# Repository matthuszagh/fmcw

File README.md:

See doc/fmcw-radar.pdf

#### TODO

* Investigate the possibility of performing FFT processing on the FPGA. This may require an FPGA
  with a higher LUT count. Investigate if the e.g. 50T is pin compatible with the current 15T. The
  goal would be to have the host computer plot the radar output in real-time rather than relying on
  post-processing. It might also be worth looking at the ECP5 FPGA, which seems to give you more per
  dollar and has better open source support.
* Formally verify FPGA code with [SymbiYosys](https://symbiyosys.readthedocs.io/en/latest/quickstart.html).
* Write PC code.
* Consider using a soft processor
  (e.g. [picorv32](https://github.com/cliffordwolf/picorv32/tree/master/picosoc)) for the FPGA
  control logic and configuration.
* Create RF simulations with OpenEMS.
* Create script to ensure all FPGA pins are connected correctly using a JTAG boundary scan.
* Modify FPGA code to allow configuration of the radar via a connected PC, rather than baking the
  logic directly into the FPGA code. This has the benefit that the FPGA logic does not need to be
  resynthesized each time the configurations are changed.
* Improve documentation.
* Remove old files only needed in the previous iteration of this project.
* 3D print mount for radar. This should include a case for the PCB and a mount for the antenna.

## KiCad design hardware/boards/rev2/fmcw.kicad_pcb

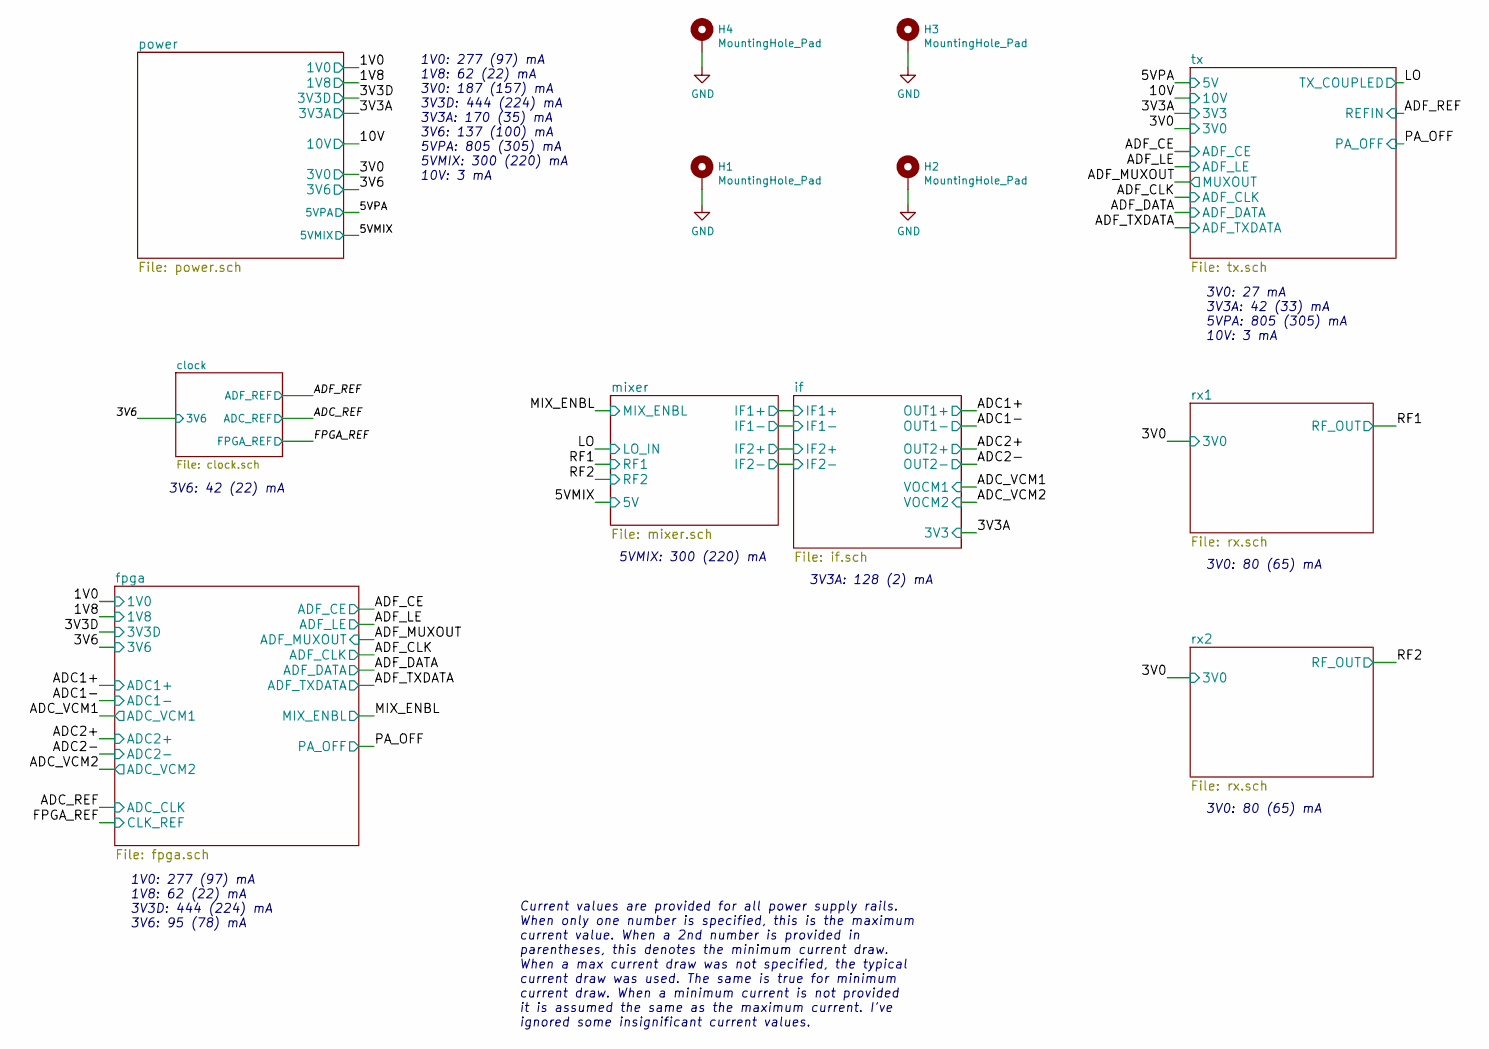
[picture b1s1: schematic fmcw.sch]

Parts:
H1, H2, H3, H4: MountingHole_Pad; MountingHole_3.2mm_M3_Pad_Via

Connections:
GND: H1.1, H2.1, H3.1, H4.1; also elsewhere on the board

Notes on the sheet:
1V0: 277 (97) mA 1V8: 62 (22) mA 3V3D: 444 (224) mA 3V6: 95 (78) mA
3V6: 42 (22) mA
1V0: 277 (97) mA 1V8: 62 (22) mA 3V0: 187 (157) mA 3V3D: 444 (224) mA 3V3A: 170 (35) mA 3V6: 137 (100) mA 5VPA: 805 (305) mA 5VMIX: 300 (220) mA 10V: 3 mA
Current values are provided for all power supply rails. When only one number is specified, this is the maximum current value. When a 2nd number is provided in parentheses, this denotes the minimum current draw. When a max current draw was not specified, the typical current draw was used. The same i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
5VMIX: 300 (220) mA
3V3A: 128 (2) mA
3V0: 27 mA 3V3A: 42 (33) mA 5VPA: 805 (305) mA 10V: 3 mA
3V0: 80 (65) mA

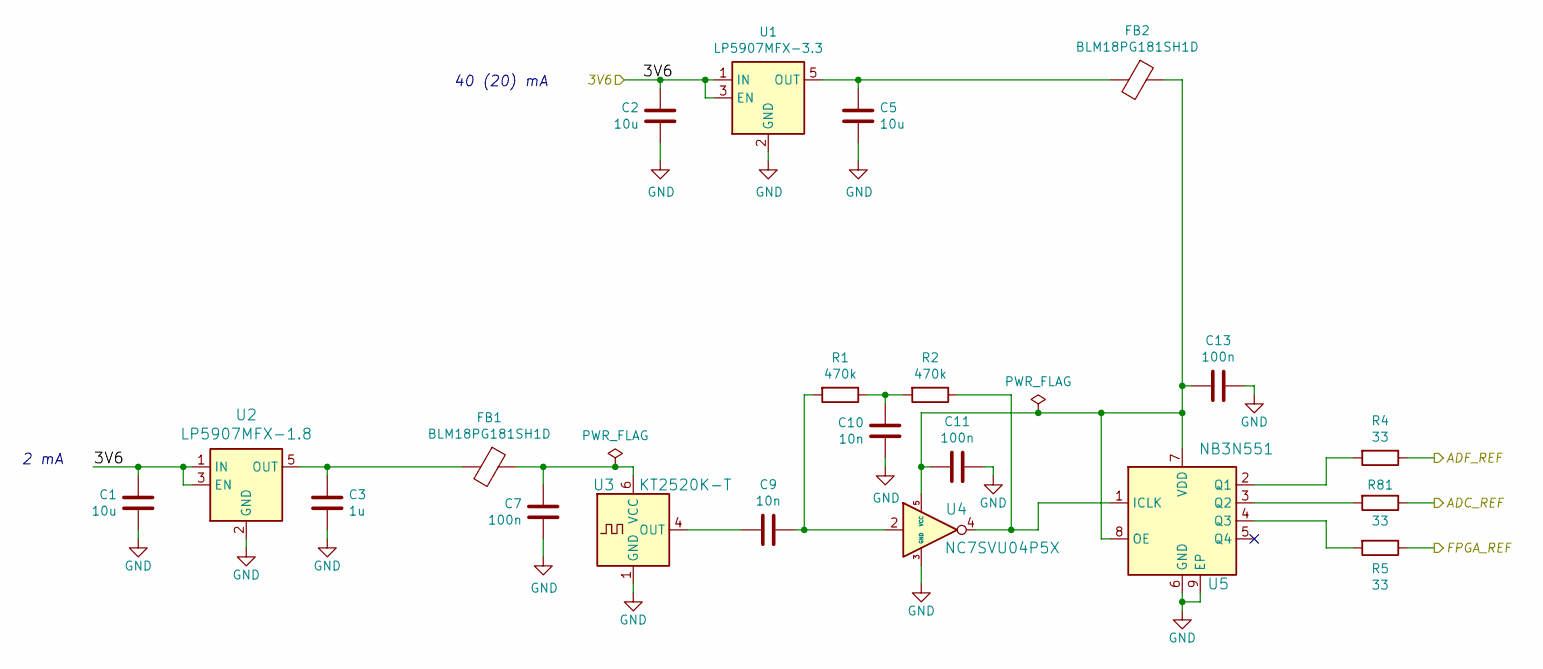
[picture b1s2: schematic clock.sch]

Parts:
C1, C2, C5: 10u; C_0805_2012Metric
C3: 1u; C_0805_2012Metric
C7, C11, C13: 100n; C_0402_1005Metric
C9, C10: 10n; C_0402_1005Metric
FB1, FB2: BLM18PG181SH1D; L_0603_1608Metric
R1, R2: 470k; R_0402_1005Metric
R4, R5, R81: 33; R_0402_1005Metric
U1: LP5907MFX-3.3; SOT-23-5
U2: LP5907MFX-1.8; SOT-23-5
U3: KT2520K-T; Oscillator_SMD_Kyocera_2520-6Pin_2.5x2.0mm
U4: NC7SVU04P5X; SOT-353_SC-70-5
U5: NB3N551; DFN-8-1EP_2x2mm_P0.5mm_EP0.9x1.3mm

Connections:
/3V6: C1.1, C2.1, U1.1 (IN), U1.3 (EN), U2.1 (IN), U2.3 (EN); also elsewhere on the board
/ADC_REF: R81.1; also elsewhere on the board
/ADF_REF: R4.1; also elsewhere on the board
/FPGA_REF: R5.1; also elsewhere on the board
GND: C1.2, C2.2, C3.2, C5.2, C7.1, C10.1, C11.1, C13.1, U1.2 (GND), U2.2 (GND), U3.1 (GND), U3.3 (GND), U4.3 (GND), U5.6 (GND), U5.9 (EP); also elsewhere on the board
unnamed: C3.1, FB1.2, U2.5 (OUT)
unnamed: C5.1, FB2.2, U1.5 (OUT)
unnamed: C7.2, FB1.1, U3.6 (VCC)
unnamed: C9.1, R1.2, U4.2
unnamed: C9.2, U3.4 (OUT)
unnamed: C10.2, R1.1, R2.2
unnamed: C11.2, C13.2, FB2.1, U4.5 (VCC), U5.7 (VDD), U5.8 (OE)
unnamed: R2.1, U4.4, U5.1 (ICLK)
unnamed: R4.2, U5.2 (Q1)
unnamed: R5.2, U5.4 (Q3)
unnamed: R81.2, U5.3 (Q2)

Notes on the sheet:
2 mA
40 (20) mA

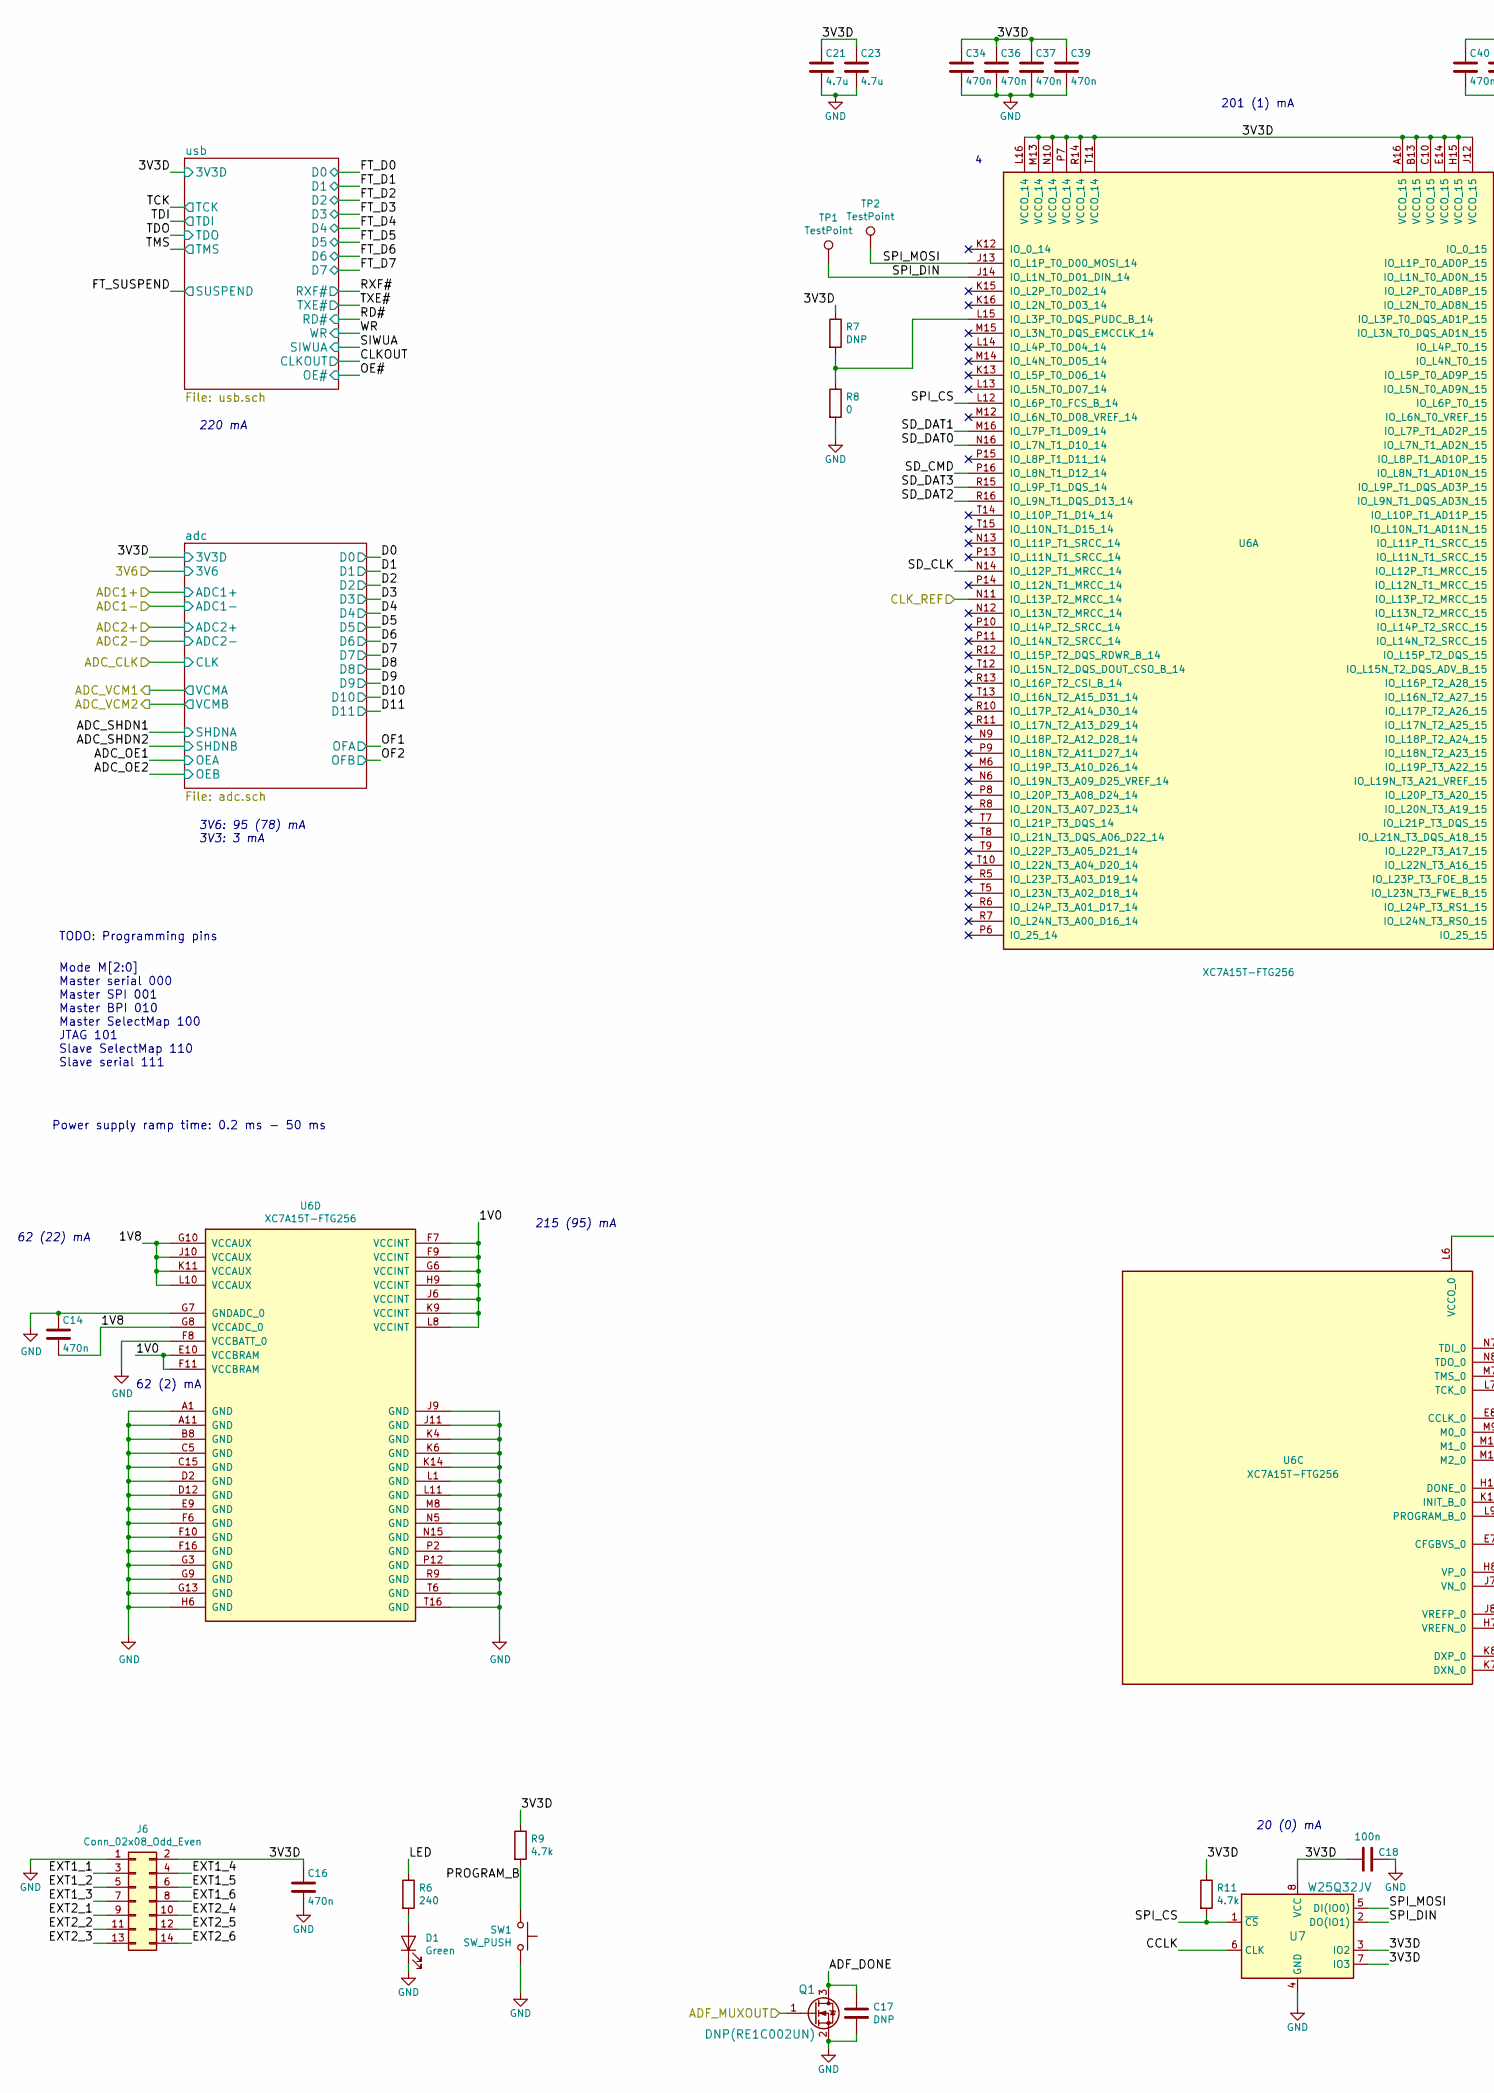
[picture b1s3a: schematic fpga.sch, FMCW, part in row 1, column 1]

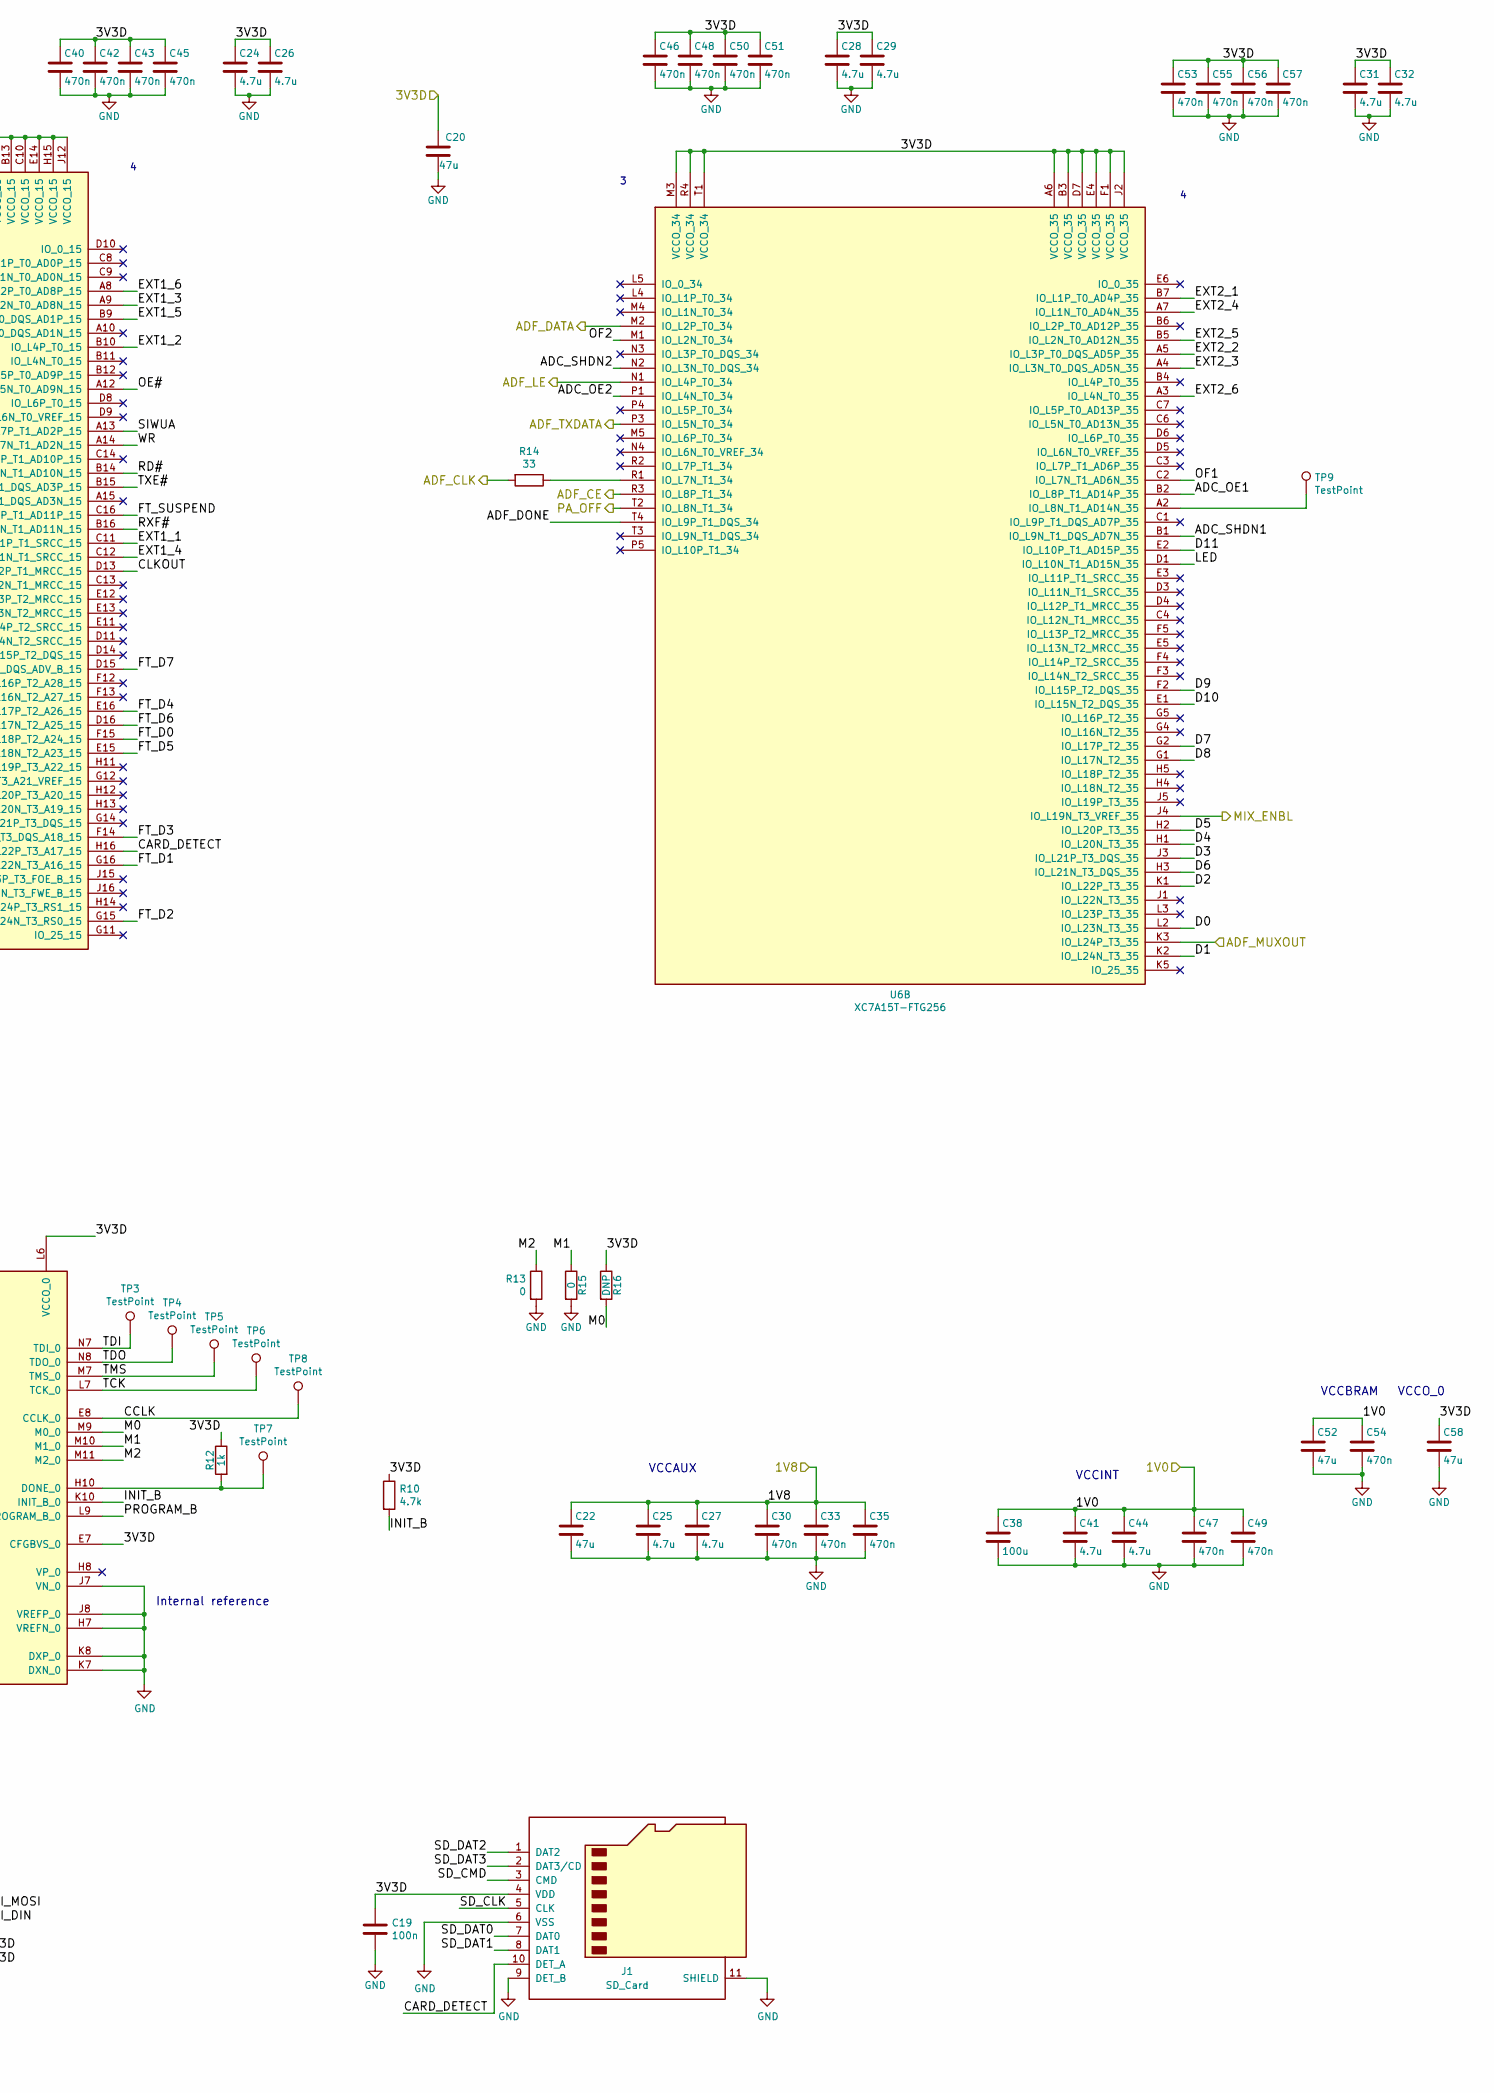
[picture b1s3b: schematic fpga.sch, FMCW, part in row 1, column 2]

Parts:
C14, C16, C30, C33, C34, C35, C36, C37, C39, C40, C42, C43, C45, C46, C47, C48, C49, C50, C51, C53, C54, C55, C56, C57: 470n; C_0603_1608Metric
C17: DNP; C_0402_1005Metric
C18, C19: 100n; C_0402_1005Metric
C20, C22, C52, C58: 47u; C_1206_3216Metric
C21, C23, C24, C25, C26, C27, C28, C29, C31, C32, C41, C44: 4.7u; C_0805_2012Metric
C38: 100u; C_1210_3225Metric
D1: Green; LED_0603_1608Metric
J1: SD_Card; microSD_HC_Hirose_DM3BT-DSF-PEJS
J6: Conn_02x08_Odd_Even; PinHeader_2x07_P2.54mm_Vertical
Q1: DNP(RE1C002UN); SOT-416
R6: 240; R_0402_1005Metric
R7, R16: DNP; R_0402_1005Metric
R8, R13, R15: 0; R_0402_1005Metric
R9, R10, R11: 4.7k; R_0402_1005Metric
R12: 1k; R_0402_1005Metric
R14: 33; R_0402_1005Metric
SW1: SW_PUSH; SW_SPST_PTS810
TP1, TP2, TP3, TP4, TP5, TP6, TP7, TP8, TP9: TestPoint; TestPoint_Loop_D1.80mm_Drill1.0mm_Beaded
U6: XC7A15T-FTG256; Xilinx_FTG256
U7: W25Q32JV; SOIJ-8_5.3x5.3mm_P1.27mm

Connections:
/1V0: C38.1, C41.1, C44.1, C47.1, C49.1, C52.1, C54.1, U6.E10 (VCCBRAM), U6.F7 (VCCINT), U6.F9 (VCCINT), U6.F11 (VCCBRAM), U6.G6 (VCCINT), U6.H9 (VCCINT), U6.J6 (VCCINT), U6.K9 (VCCINT), U6.L8 (VCCINT); also elsewhere on the board
/1V8: C14.2, C22.1, C25.1, C27.1, C30.1, C33.1, C35.1, U6.G8 (VCCADC_0), U6.G10 (VCCAUX), U6.J10 (VCCAUX), U6.K11 (VCCAUX), U6.L10 (VCCAUX); also elsewhere on the board
/ADF_CE: U6.R3 (IO_L8P_T1_34); also elsewhere on the board
/ADF_CLK: R14.2; also elsewhere on the board
/ADF_DATA: U6.M2 (IO_L2P_T0_34); also elsewhere on the board
/ADF_LE: U6.N1 (IO_L4P_T0_34); also elsewhere on the board
/ADF_MUXOUT: Q1.1 (G), U6.K3 (IO_L24P_T3_35); also elsewhere on the board
/ADF_TXDATA: U6.P3 (IO_L5N_T0_34); also elsewhere on the board
/FPGA_REF: U6.N11 (IO_L13P_T2_MRCC_14); also elsewhere on the board
/MIX_ENBL: U6.J4 (IO_L19N_T3_VREF_35); also elsewhere on the board
/PA_OFF: U6.T2 (IO_L8N_T1_34); also elsewhere on the board
/fpga/ADC_OE1: U6.B2 (IO_L8P_T1_AD14P_35); also elsewhere on the board
/fpga/ADC_OE2: U6.P1 (IO_L4N_T0_34); also elsewhere on the board
/fpga/ADC_SHDN1: U6.B1 (IO_L9N_T1_DQS_AD7N_35); also elsewhere on the board
/fpga/ADC_SHDN2: U6.N2 (IO_L3N_T0_DQS_34); also elsewhere on the board
/fpga/ADF_DONE: C17.1, Q1.3 (D), U6.T4 (IO_L9P_T1_DQS_34)
/fpga/CARD_DETECT: J1.10 (DET_A), U6.H16 (IO_L22P_T3_A17_15)
/fpga/CCLK: TP8.1, U6.E8 (CCLK_0), U7.6 (CLK)
/fpga/CLKOUT: U6.D13 (IO_L12P_T1_MRCC_15); also elsewhere on the board
/fpga/D0: U6.L2 (IO_L23N_T3_35); also elsewhere on the board
/fpga/D1: U6.K2 (IO_L24N_T3_35); also elsewhere on the board
/fpga/D2: U6.K1 (IO_L22P_T3_35); also elsewhere on the board
/fpga/D3: U6.J3 (IO_L21P_T3_DQS_35); also elsewhere on the board
/fpga/D4: U6.H1 (IO_L20N_T3_35); also elsewhere on the board
/fpga/D5: U6.H2 (IO_L20P_T3_35); also elsewhere on the board
/fpga/D6: U6.H3 (IO_L21N_T3_DQS_35); also elsewhere on the board
/fpga/D7: U6.G2 (IO_L17P_T2_35); also elsewhere on the board
/fpga/D8: U6.G1 (IO_L17N_T2_35); also elsewhere on the board
/fpga/D9: U6.F2 (IO_L15P_T2_DQS_35); also elsewhere on the board
/fpga/D10: U6.E1 (IO_L15N_T2_DQS_35); also elsewhere on the board
/fpga/D11: U6.E2 (IO_L10P_T1_AD15P_35); also elsewhere on the board
/fpga/EXT1_1: J6.3, U6.C11 (IO_L11P_T1_SRCC_15)
/fpga/EXT1_2: J6.5, U6.B10 (IO_L4P_T0_15)
/fpga/EXT1_3: J6.7, U6.A9 (IO_L2N_T0_AD8N_15)
/fpga/EXT1_4: J6.4, U6.C12 (IO_L11N_T1_SRCC_15)
/fpga/EXT1_5: J6.6, U6.B9 (IO_L3P_T0_DQS_AD1P_15)
/fpga/EXT1_6: J6.8, U6.A8 (IO_L2P_T0_AD8P_15)
/fpga/EXT2_1: J6.9, U6.B7 (IO_L1P_T0_AD4P_35)
/fpga/EXT2_2: J6.11, U6.A5 (IO_L3P_T0_DQS_AD5P_35)
/fpga/EXT2_3: J6.13, U6.A4 (IO_L3N_T0_DQS_AD5N_35)
/fpga/EXT2_4: J6.10, U6.A7 (IO_L1N_T0_AD4N_35)
/fpga/EXT2_5: J6.12, U6.B5 (IO_L2N_T0_AD12N_35)
/fpga/EXT2_6: J6.14, U6.A3 (IO_L4N_T0_35)
/fpga/FT_D0: U6.F15 (IO_L18P_T2_A24_15); also elsewhere on the board
/fpga/FT_D1: U6.G16 (IO_L22N_T3_A16_15); also elsewhere on the board
/fpga/FT_D2: U6.G15 (IO_L24N_T3_RS0_15); also elsewhere on the board
/fpga/FT_D3: U6.F14 (IO_L21N_T3_DQS_A18_15); also elsewhere on the board
/fpga/FT_D4: U6.E16 (IO_L17P_T2_A26_15); also elsewhere on the board
/fpga/FT_D5: U6.E15 (IO_L18N_T2_A23_15); also elsewhere on the board
/fpga/FT_D6: U6.D16 (IO_L17N_T2_A25_15); also elsewhere on the board
/fpga/FT_D7: U6.D15 (IO_L15N_T2_DQS_ADV_B_15); also elsewhere on the board
/fpga/FT_SUSPEND: U6.C16 (IO_L10P_T1_AD11P_15); also elsewhere on the board
/fpga/INIT_B: R10.2, U6.K10 (INIT_B_0)
/fpga/LED: R6.1, U6.D1 (IO_L10N_T1_AD15N_35)
/fpga/M0: R16.2, U6.M9 (M0_0)
/fpga/M1: R15.1, U6.M10 (M1_0)
/fpga/M2: R13.1, U6.M11 (M2_0)
/fpga/OE#: U6.A12 (IO_L5N_T0_AD9N_15); also elsewhere on the board
/fpga/OF1: U6.C2 (IO_L7N_T1_AD6N_35); also elsewhere on the board
/fpga/OF2: U6.M1 (IO_L2N_T0_34); also elsewhere on the board
/fpga/PROGRAM_B: R9.2, SW1.1, U6.L9 (PROGRAM_B_0)
/fpga/RD#: U6.B14 (IO_L8N_T1_AD10N_15); also elsewhere on the board
/fpga/RXF#: U6.B16 (IO_L10N_T1_AD11N_15); also elsewhere on the board
/fpga/SD_CLK: J1.5 (CLK), U6.N14 (IO_L12P_T1_MRCC_14)
/fpga/SD_CMD: J1.3 (CMD), U6.P16 (IO_L8N_T1_D12_14)
/fpga/SD_DAT0: J1.7 (DAT0), U6.N16 (IO_L7N_T1_D10_14)
/fpga/SD_DAT1: J1.8 (DAT1), U6.M16 (IO_L7P_T1_D09_14)
/fpga/SD_DAT2: J1.1 (DAT2), U6.R16 (IO_L9N_T1_DQS_D13_14)
/fpga/SD_DAT3: J1.2 (DAT3/CD), U6.R15 (IO_L9P_T1_DQS_14)
/fpga/SIWUA: U6.A13 (IO_L7P_T1_AD2P_15); also elsewhere on the board
/fpga/SPI_CS: R11.2, U6.L12 (IO_L6P_T0_FCS_B_14), U7.1 (~CS)
/fpga/SPI_DIN: TP1.1, U6.J14 (IO_L1N_T0_D01_DIN_14), U7.2 (DO(IO1))
/fpga/SPI_MOSI: TP2.1, U6.J13 (IO_L1P_T0_D00_MOSI_14), U7.5 (DI(IO0))
/fpga/TCK: TP6.1, U6.L7 (TCK_0); also elsewhere on the board
/fpga/TDI: TP3.1, U6.N7 (TDI_0); also elsewhere on the board
/fpga/TDO: TP4.1, U6.N8 (TDO_0); also elsewhere on the board
/fpga/TMS: TP5.1, U6.M7 (TMS_0); also elsewhere on the board
/fpga/TXE#: U6.B15 (IO_L9P_T1_DQS_AD3P_15); also elsewhere on the board
/fpga/WR: U6.A14 (IO_L7N_T1_AD2N_15); also elsewhere on the board
GND: C14.1, C16.2, C17.2, C18.1, C19.2, C20.2, C21.2, C22.2, C23.2, C24.2, C25.2, C26.2, C27.2, C28.2, C29.2, C30.2, C31.2, C32.2, C33.2, C34.2, C35.2, C36.2, C37.2, C38.2, C39.2, C40.2, C41.2, C42.2, C43.2, C44.2, C45.2, C46.2, C47.2, C48.2, C49.2, C50.2, C51.2, C52.2, C53.2, C54.2, C55.2, C56.2, C57.2, C58.2, D1.1 (K), J1.6 (VSS), J1.9 (DET_B), J1.11 (SHIELD), J6.1, Q1.2 (S), R8.2, R13.2, R15.2, SW1.2, U6.A1 (GND), U6.A11 (GND), U6.B8 (GND), U6.C5 (GND), U6.C15 (GND), U6.D2 (GND), U6.D12 (GND), U6.E9 (GND), U6.F6 (GND), U6.F8 (VCCBATT_0), U6.F10 (GND), U6.F16 (GND), U6.G3 (GND), U6.G7 (GNDADC_0), U6.G9 (GND), U6.G13 (GND), U6.H6 (GND), U6.H7 (VREFN_0), U6.J7 (VN_0), U6.J8 (VREFP_0), U6.J9 (GND), U6.J11 (GND), U6.K4 (GND), U6.K6 (GND), U6.K7 (DXN_0), U6.K8 (DXP_0), U6.K14 (GND), U6.L1 (GND), U6.L11 (GND), U6.M8 (GND), U6.N5 (GND), U6.N15 (GND), U6.P2 (GND), U6.P12 (GND), U6.R9 (GND), U6.T6 (GND), U6.T16 (GND), U7.4 (GND); also elsewhere on the board
unnamed: D1.2 (A), R6.2
unnamed: R7.2, R8.1, U6.L15 (IO_L3P_T0_DQS_PUDC_B_14)
unnamed: R12.2, TP7.1, U6.H10 (DONE_0)
unnamed: R14.1, U6.R1 (IO_L7N_T1_34)
unnamed: TP9.1, U6.A2 (IO_L8N_T1_AD14N_35)

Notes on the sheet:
62 (22) mA
Power supply ramp time: 0.2 ms - 50 ms
TODO: Programming pins
Mode M[2:0] Master serial 000 Master SPI 001 Master BPI 010 Master SelectMap 100 JTAG 101 Slave SelectMap 110 Slave serial 111
62 (2) mA
220 mA
3V6: 95 (78) mA 3V3: 3 mA
215 (95) mA
201 (1) mA
20 (0) mA
Internal reference
VCCAUX
VCCINT
VCCBRAM
VCCO_0

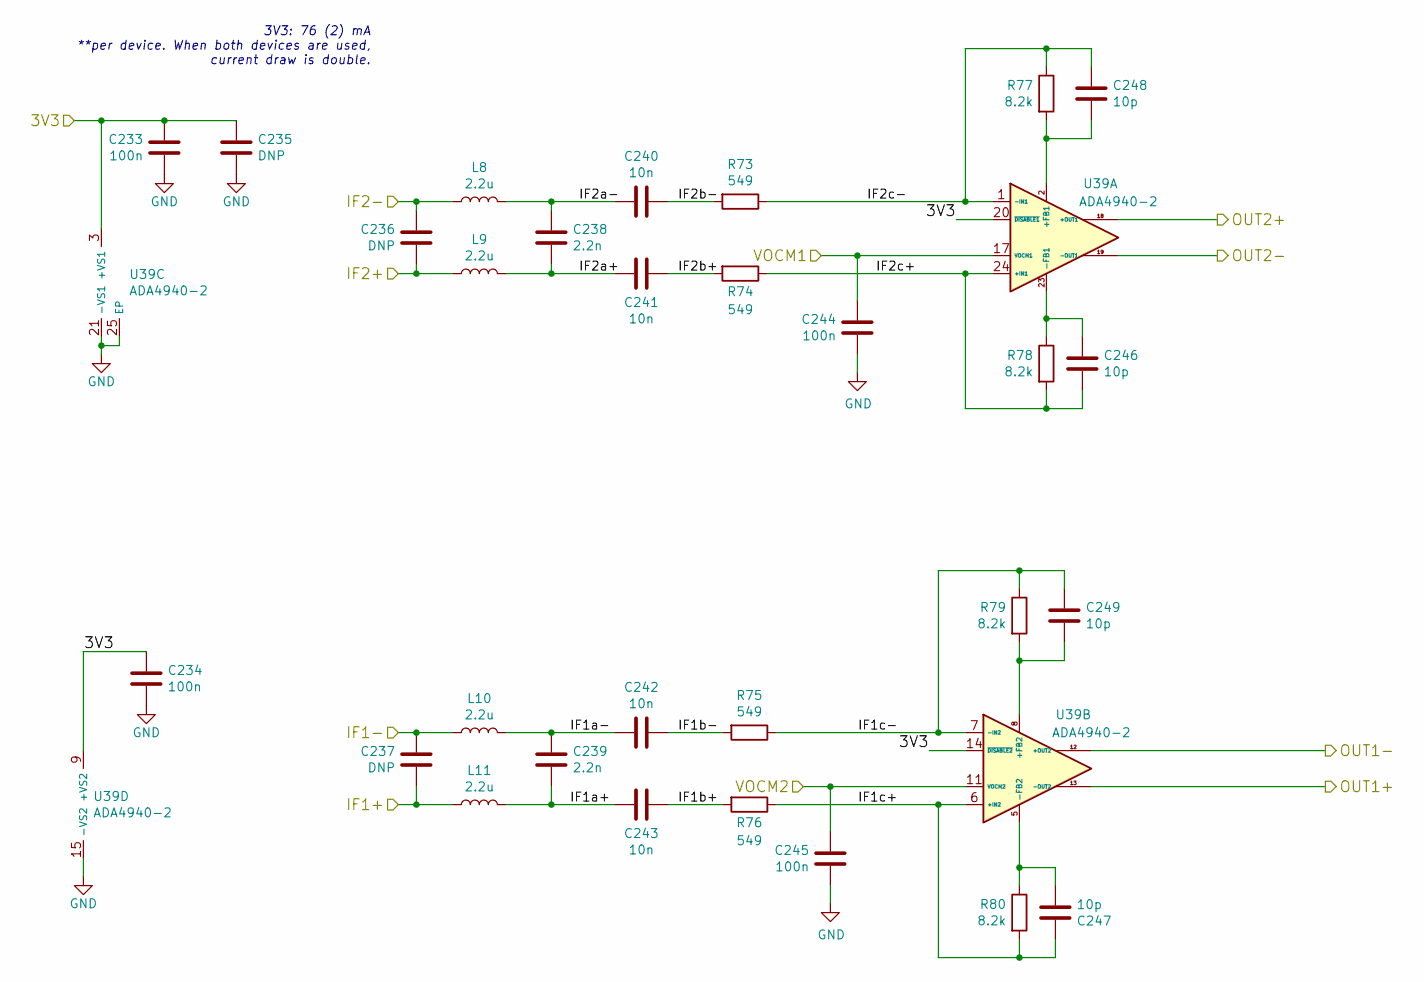
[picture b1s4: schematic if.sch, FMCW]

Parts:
C233, C234, C244, C245: 100n; C_0402_1005Metric
C235: DNP; C_0805_2012Metric
C236, C237: DNP; C_0402_1005Metric
C238, C239: 2.2n; C_0402_1005Metric
C240, C241, C242, C243: 10n; C_0402_1005Metric
C246, C247, C248, C249: 10p; C_0402_1005Metric
L8, L9, L10, L11: 2.2u; L_0603_1608Metric
R73, R74, R75, R76: 549; R_0402_1005Metric
R77, R78, R79, R80: 8.2k; R_0402_1005Metric
U39: ADA4940-2; LFCSP-24-1EP_4x4mm_P0.5mm_EP2.5x2.5mm_ThermalVias

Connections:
/3V3A: C233.1, C234.1, C235.1, U39.3 (+VS1), U39.4 (+VS1), U39.9 (+VS2), U39.10 (+VS2), U39.14 (~DISABLE2), U39.20 (~DISABLE1); also elsewhere on the board
/ADC1+: U39.13 (-OUT2); also elsewhere on the board
/ADC1-: U39.12 (+OUT2); also elsewhere on the board
/ADC2+: U39.18 (+OUT1); also elsewhere on the board
/ADC2-: U39.19 (-OUT1); also elsewhere on the board
/ADC_VCM1: C244.1, U39.17 (VOCM1); also elsewhere on the board
/ADC_VCM2: C245.1, U39.11 (VOCM2); also elsewhere on the board
/if/IF1+: C237.2, L11.1; also elsewhere on the board
/if/IF1-: C237.1, L10.1; also elsewhere on the board
/if/IF1a+: C239.2, C243.2, L11.2
/if/IF1a-: C239.1, C242.2, L10.2
/if/IF1b+: C243.1, R76.2
/if/IF1b-: C242.1, R75.2
/if/IF1c+: C247.1, R76.1, R80.2, U39.6 (+IN2)
/if/IF1c-: C249.1, R75.1, R79.1, U39.7 (-IN2)
/if/IF2+: C236.2, L9.1; also elsewhere on the board
/if/IF2-: C236.1, L8.1; also elsewhere on the board
/if/IF2a+: C238.2, C241.2, L9.2
/if/IF2a-: C238.1, C240.2, L8.2
/if/IF2b+: C241.1, R74.2
/if/IF2b-: C240.1, R73.2
/if/IF2c+: C246.2, R74.1, R78.2, U39.24 (+IN1)
/if/IF2c-: C248.1, R73.1, R77.1, U39.1 (-IN1)
GND: C233.2, C234.2, C235.2, C244.2, C245.2, U39.15 (-VS2), U39.16 (-VS2), U39.21 (-VS1), U39.22 (-VS1), U39.25 (EP); also elsewhere on the board
unnamed: C246.1, R78.1, U39.23 (-FB1)
unnamed: C247.2, R80.1, U39.5 (-FB2)
unnamed: C248.2, R77.2, U39.2 (+FB1)
unnamed: C249.2, R79.2, U39.8 (+FB2)

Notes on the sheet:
3V3: 76 (2) mA **per device. When both devices are used, current draw is double.

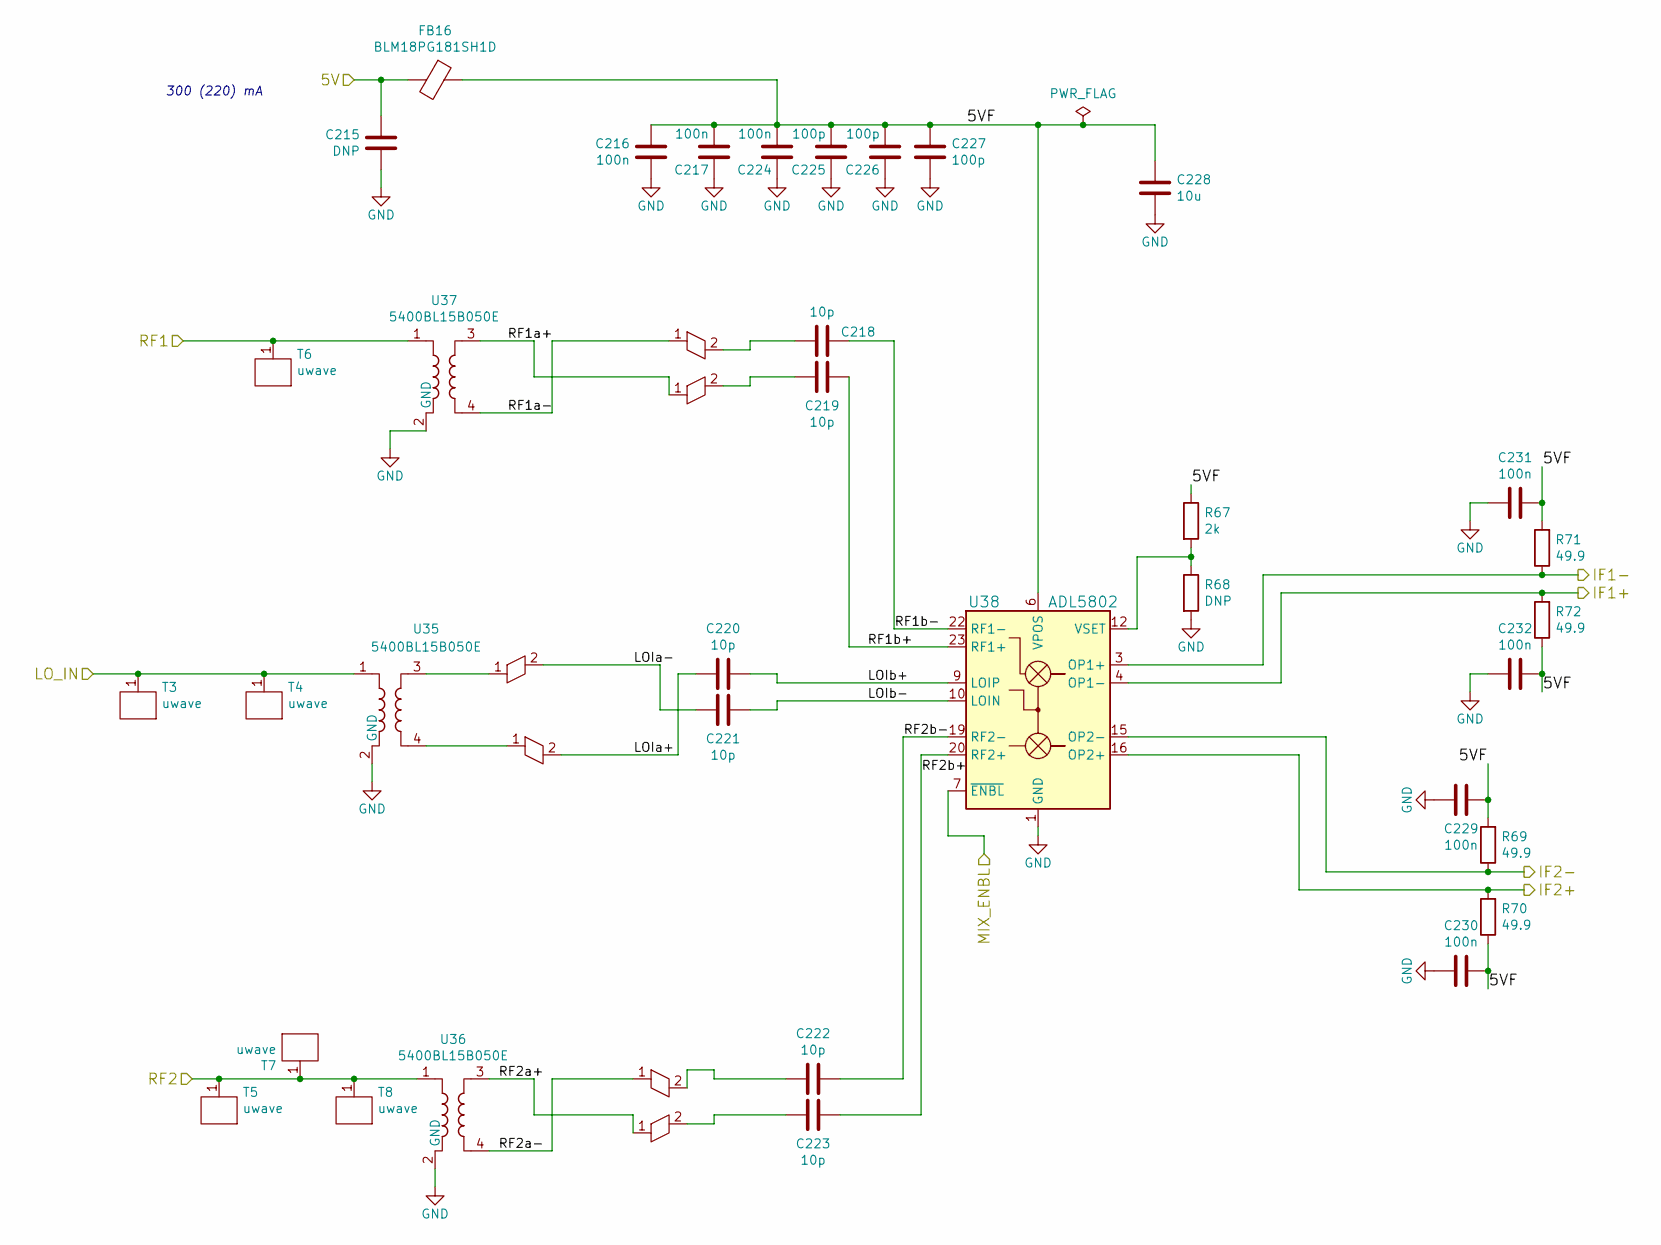
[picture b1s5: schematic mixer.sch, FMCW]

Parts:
C215: DNP; C_0805_2012Metric
C216, C217, C224, C229, C230, C231, C232: 100n; C_0402_1005Metric
C218, C219, C220, C221, C222, C223: 10p; RF_C_0201_0603Metric
C225, C226, C227: 100p; C_0402_1005Metric
C228: 10u; C_0805_2012Metric
FB16: BLM18PG181SH1D; L_0603_1608Metric
JP2, JP4, JP17: balun_exit_inv
JP3, JP5, JP18: balun_exit
R67: 2k; R_0402_1005Metric
R68: DNP; R_0402_1005Metric
R69, R70, R71, R72: 49.9; R_0402_1005Metric
T3, T4, T5, T6, T7, T8: uwave; uwm_0.38_0.17_90
U35, U36, U37: 5400BL15B050E; Balun_Johanson_5400BL15B050E
U38: ADL5802; LFCSP-24-1EP_4x4mm_P0.5mm_EP2.5x2.5mm_ThermalVias

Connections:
/5VMIX: C215.2, FB16.2; also elsewhere on the board
/LO: T3.1, T4.1, U35.1; also elsewhere on the board
/MIX_ENBL: U38.7 (~ENBL); also elsewhere on the board
/RF1: T6.1, U37.1; also elsewhere on the board
/RF2: T5.1, T7.1, T8.1, U36.1; also elsewhere on the board
/if/IF1+: R72.2, U38.4 (OP1-); also elsewhere on the board
/if/IF1-: R71.1, U38.3 (OP1+); also elsewhere on the board
/if/IF2+: R70.2, U38.16 (OP2+); also elsewhere on the board
/if/IF2-: R69.1, U38.15 (OP2-); also elsewhere on the board
/mixer/5VF: C216.2, C217.2, C224.2, C225.2, C226.2, C227.2, C228.2, C229.2, C230.2, C231.2, C232.2, FB16.1, R67.1, R69.2, R70.1, R71.2, R72.1, U38.6 (VPOS), U38.13 (VPOS), U38.24 (VPOS)
/mixer/LOIa+: C220.2, JP18.1, JP18.2, U35.4; also elsewhere on the board
/mixer/LOIa-: C221.2, JP17.1, JP17.2, U35.3; also elsewhere on the board
/mixer/LOIb+: C220.1, U38.9 (LOIP)
/mixer/LOIb-: C221.1, U38.10 (LOIN)
/mixer/RF1a+: C219.2, JP4.1, JP4.2, U37.3; also elsewhere on the board
/mixer/RF1a-: C218.2, JP5.1, JP5.2, U37.4; also elsewhere on the board
/mixer/RF1b+: C219.1, U38.23 (RF1+)
/mixer/RF1b-: C218.1, U38.22 (RF1-)
/mixer/RF2a+: C223.2, JP2.1, JP2.2, U36.3; also elsewhere on the board
/mixer/RF2a-: C222.2, JP3.1, JP3.2, U36.4; also elsewhere on the board
/mixer/RF2b+: C223.1, U38.20 (RF2+)
/mixer/RF2b-: C222.1, U38.19 (RF2-)
GND: C215.1, C216.1, C217.1, C224.1, C225.1, C226.1, C227.1, C228.1, C229.1, C230.1, C231.1, C232.1, R68.2, U35.2 (GND), U35.5 (GND), U36.2 (GND), U36.5 (GND), U37.2 (GND), U37.5 (GND), U38.1 (GND), U38.2 (GND), U38.5 (GND), U38.8 (GND), U38.11 (GND), U38.14 (GND), U38.17 (GND), U38.18 (GND), U38.21 (GND), U38.25 (GND); also elsewhere on the board
unnamed: R67.2, R68.1, U38.12 (VSET)

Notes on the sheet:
300 (220) mA
